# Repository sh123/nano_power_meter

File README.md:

# Introduction
Dual channel Arduino Nano RF milliwatt power meter for HF/VHF/UHF/SHF bands. Can be used for power measurement, different RF equipment troubleshooting, RF leakage search and antenna radiation/gain measurements and comparison.

This project is Arduino Nano clone of W1GHZ power meter adopted for use with Arduino Nano and SSD1307 OLED screen. Read more details at http://www.w1ghz.org/new/portable_powermeter.pdf.

Unlike original meter, which is just an indicator, this device shows precise dBm values and could be calibrated, calibration table is stored in the sketch. Moreover, device takes maximum RF power value during 1 second interval, which allows signal duration measurements down to 1 ms and marks maximum value during 1 minute interval on the bar.

# Technical details
- Measurement power range from -32 up to 20 dBm on channel A and -60 up to 20 dBm on channel B, with external attenuator could be used for larger values.
- Frequency range
  - Channel A: 300 MHz - 7 GHz, up to 12 GHz with performance degradation
  - Channel B: 10 KHz up to 300 MHz
- Minimum signal length detection about 1 ms
- Based on Arduino Nano
- Screen is [SSD1307](https://cdn-shop.adafruit.com/datasheets/SSD1306.pdf)
- UHF/SHF part (left channel A) is based [LTC5507 RF Power Detector](https://www.analog.com/media/en/technical-documentation/data-sheets/5508fa.pdf), allows measurement from 300MHz up to 7GHz and up to approximately 12 GHz with some performance degradation.
- HF/VHF part (right channel B) is based on [AD8307 Logarithmic Amplifier](https://www.analog.com/media/en/technical-documentation/data-sheets/AD8307.pdf), allows mesurement from DC up to 300 MHz
- Geiger counter style buzzer for audiable signal level indication
- Must be powered from the battery (e.g. 9V)

# Building
User platformio to build and upload.

# Results
Sucessfully shows power values for various ISM signals, such as 5 GHz, 2.4 GHz WiFi, Bluetooth, 433/868 MHz ISM devices at close range and amateur radio transmissions at HF.

At SHF band good sensitivity and results are achieved when using cheap Vivaldi antenna. 

At HF/VHF/UHF telescopic antenna performs well enough. For close board inspection EM probes could be used. 

Also, additional shield could be helpful. 

Device must be powered from the battery only, powering from PC USB will cause PC USB RFI and other noise to be measured by the device.

Signals with larger than +20 dBm levels could be measured with additional external attenuator.

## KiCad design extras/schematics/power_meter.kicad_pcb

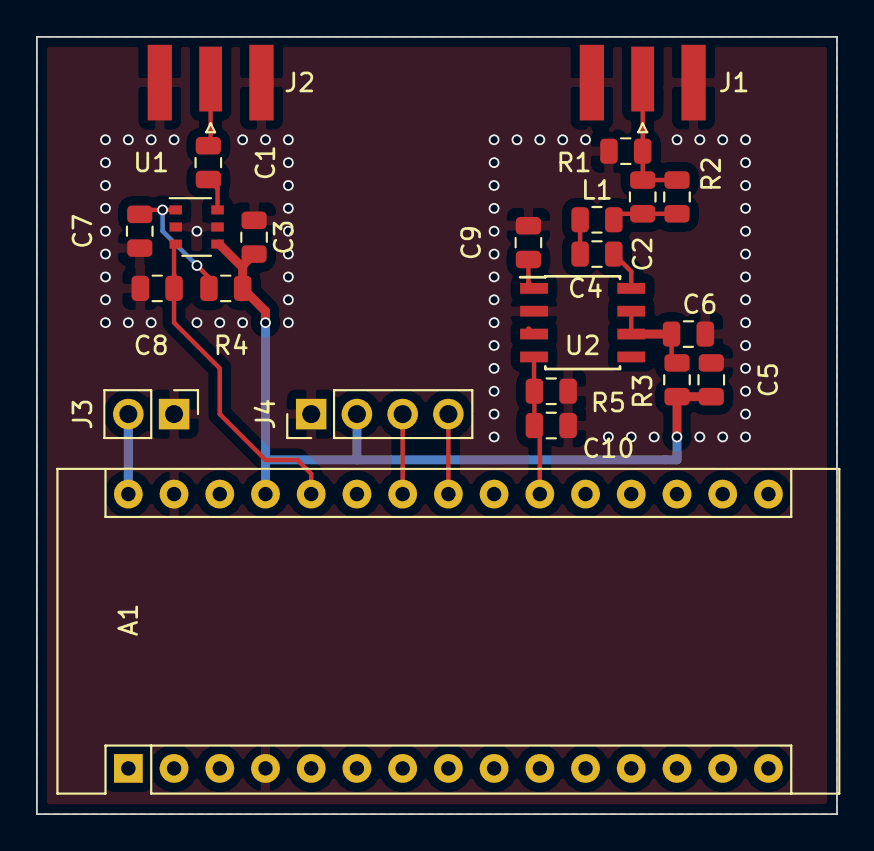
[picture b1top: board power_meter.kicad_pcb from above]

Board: 2 copper layers, 44.5 x 43.2 mm, 23 parts (0 on the bottom side), 16 nets.

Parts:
A1: Arduino_Nano_v3.x; Arduino_Nano
C1: 8.2pF; C_0805_2012Metric
C2: 15pF; C_0805_2012Metric
C3, C7, C8, C10: 0.1uF; C_0805_2012Metric
C4: .01uF; C_0805_2012Metric
C5: 100pF; C_0805_2012Metric
C6, C9: C; C_0805_2012Metric
J1: RF_UHF; SMA_Samtec_SMA-J-P-H-ST-EM1_EdgeMount
J2: RF_SHF; SMA_Samtec_SMA-J-P-H-ST-EM1_EdgeMount
J3: Conn_01x02; PinHeader_1x02_P2.54mm_Vertical
J4: Conn_01x04; PinHeader_1x04_P2.54mm_Vertical
L1: L; L_0805_2012Metric
R1: 51; R_0805_2012Metric
R2, R3, R5: R; R_0805_2012Metric
R4: 10k; R_0805_2012Metric
U1: ltc5508; TSOP-6_1.65x3.05mm_P0.95mm
U2: ad8307; SOIC-8_3.9x4.9mm_P1.27mm

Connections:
+5V: A1.27, C3.2, C5.2, J4.2, R3.1, R4.2, U1.4
+9V: A1.30, J3.2
GND: A1.4, A1.29, C3.1, C5.1, C6.2, C7.2, C8.2, C9.1, C10.2, J1.2, J2.2, J3.1, J4.1, R1.2, R5.2, U1.2, U1.5, U2.2
unnamed: C1.1, J2.1
unnamed: C1.2, U1.6
unnamed: C2.1, L1.2, R2.1
unnamed: C2.2, J1.1, R1.1, R2.2
unnamed: C4.1, U2.8
unnamed: C4.2, L1.1
unnamed: C6.1, R3.2, U2.6, U2.7
unnamed: C7.1, R4.1, U1.1
unnamed: C9.2, U2.1
RF_SHF: A1.26, C8.1, U1.3
RF_UHF: A1.21, C10.1, R5.1, U2.4
SCL: A1.24, J4.3
SDA: A1.23, J4.4

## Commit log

2020-12-13 Added schematics and Arduino sketch
2020-12-13 Added images
2020-12-13 Updated missed component values
2020-12-13 Update calibration table
2020-12-14 One more picture
2020-12-15 Added 1M maximum mark
2020-12-15 Better bar layout
2020-12-15 Change analog in pin for HF
2020-12-15 Fix bug with bar scale
2020-12-18 Added calibration for second channel
2020-12-18 Bar fixes
2020-12-18 Fix small bug
2020-12-19 Small refactoring
2020-12-28 Added case
2021-01-03 Add support for buzzer
2021-01-03 Update buzzer logic
2021-01-07 Added one more image
2021-01-07 Scaled image
2021-01-09 Implement periodic buzzer with lower period on higher signal
2021-01-12 Updated device image
2022-01-19 Updated calibration tables and minimum buzzer values
2023-03-16 Set relative path
2023-03-16 Add gerber files
2023-03-16 Moved project to platformio
2024-11-01 Added missing files
